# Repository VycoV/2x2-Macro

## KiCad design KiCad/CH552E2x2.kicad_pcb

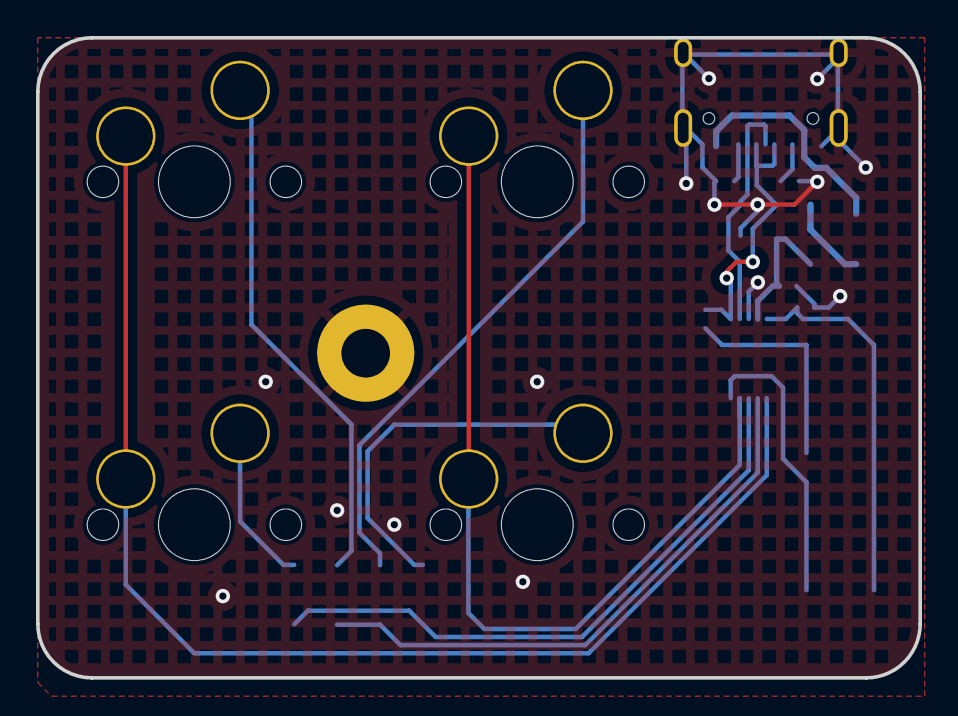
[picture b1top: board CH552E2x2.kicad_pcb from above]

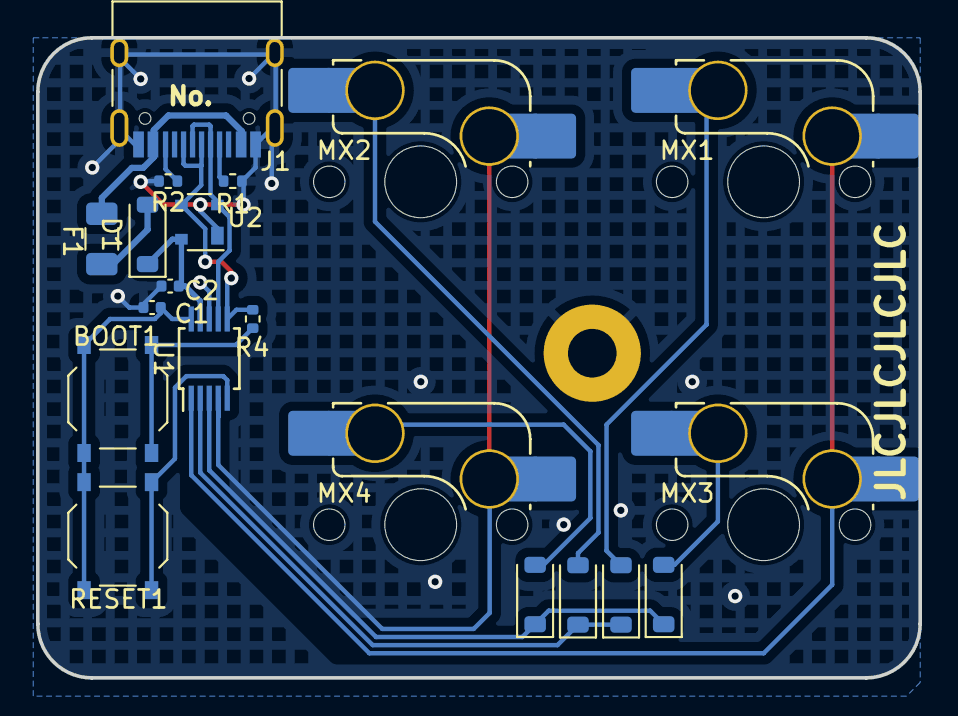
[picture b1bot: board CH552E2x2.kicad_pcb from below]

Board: 2 copper layers, 49.0 x 35.6 mm, 21 parts (20 on the bottom side), 19 nets.

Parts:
BOOT1: Switch; SW_Push_1P1T_XKB_TS-1187A
C1, C2: 100nF; C_0402_1005Metric
D1: PMEG2010EA; D_SOD-123
D3, D4, D5, D6: 1N4148; D_SOD-123
F1: 500mA; Fuse_1206_3216Metric
H1: MountingHole_Pad; MountingHole_2.7mm_M2.5_Pad
J1: USB_C_Receptacle_USB2.0; USB_C_Receptacle_HRO_TYPE-C-31-M-12
MX1, MX2, MX3, MX4: MX-NoLED; SW_MX_HS_CPG151101S11_1u
R1, R2: 5.1k; R_0402_1005Metric
R4: 10k; R_0402_1005Metric
RESET1: Switch; SW_Push_1P1T_XKB_TS-1187A
U1: CH552E; MSOP-10_3x3mm_P0.5mm
U2: PRTR5V0U2X; SOT-143

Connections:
+3V3: BOOT1.2, C1.1, RESET1.2, U1.10 (V33)
+5V: C2.1, D1.1 (K), U1.9 (VCC), U2.4 (VCC)
BOOT: BOOT1.1, R4.2
CC1: J1.A5 (CC1), R1.1
CC2: J1.B5 (CC2), R2.1
COL0: MX1.1 (COL), MX3.1 (COL), U1.1 (P1.4)
COL1: MX2.1 (COL), MX4.1 (COL), U1.4 (P1.7)
GND: C1.2, C2.2, H1.1, J1.A1 (GND), J1.A12 (GND), J1.B1 (GND), J1.B12 (GND), J1.S1 (SHIELD), R1.2, R2.2, U1.8 (GND), U2.1 (GND)
unnamed: D1.2 (A), F1.1
unnamed: D3.2 (A), MX1.2 (ROW)
unnamed: D4.2 (A), MX2.2 (ROW)
unnamed: D5.2 (A), MX3.2 (ROW)
unnamed: D6.2 (A), MX4.2 (ROW)
ROW0: D3.1 (K), D4.1 (K), U1.2 (P1.5)
ROW1: D5.1 (K), D6.1 (K), U1.3 (P1.6)
RST: RESET1.1, U1.5 (RST)
UDM: J1.A7 (D-), J1.B7 (D-), U1.7 (UDM), U2.2 (I/O1)
UDP: J1.A6 (D+), J1.B6 (D+), R4.1, U1.6 (UDP), U2.3 (I/O2)
VBUS: F1.2, J1.A4 (VBUS), J1.A9 (VBUS), J1.B4 (VBUS), J1.B9 (VBUS)

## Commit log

2024-03-07 Added Files
    Added FAK Firmware files
2024-03-07 Remove Silkscreen
    Removed Silkscreen
2024-03-10 Update
    Solder -> Hot Swap
    THT -> SMD Diodes
    Screw Hole -> Not Inconvenient Anymore
